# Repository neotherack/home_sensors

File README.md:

# Home Sensors

Monitorización ambiental de la casa con sensores ESP32, Prometheus y Grafana.

## Arquitectura

```
┌────────────────────────────────────────────────────────┐
│  ESP32 sensors (4)                                     │
│  ┌──────────┐ ┌──────────┐ ┌──────────┐ ┌──────────┐ │
│  │ Office   │ │ Master   │ │ Living   │ │ Kitchen  │ │
│  │ .178:8000│ │ .179:8000│ │ .180:8000│ │ .181:8000│ │
│  └────┬─────┘ └────┬─────┘ └────┬─────┘ └────┬─────┘ │
│       │            │            │            │        │
└───────┼────────────┼────────────┼────────────┼────────┘
        └──────┬─────┴─────┬─────┴─────┬──────┘
               │                         │
        ┌──────▼──────┐          ┌──────▼──────┐
        │  Prometheus  │          │   Grafana   │
        │  arrakis:9090│◄────────►│  (dashboard)│
        └─────────────┘          └─────────────┘
               │
        ┌──────▼──────┐
        │  Alertmanager│
        │  arrakis:9093│
        └─────────────┘
```

Todos los ESP32 exponen métricas Prometheus en `:8000/metrics`. Prometheus scrapea cada 5m.

## Sensores

| IP | Ubicación | Ambiente | Orientación | Sensores |
|---|---|---|---|---|
| `192.168.1.178:8000` | **Office** | indoor | west | BMP180 (temp, pres), DHT22 (temp, hum), MICS5524 (gas ppm) |
| `192.168.1.179:8000` | **Master bedroom** | indoor | east | DHT22 (temp, hum) |
| `192.168.1.180:8000` | **Living** | indoor | east | DHT22 (temp, hum) |
| `192.168.1.181:8000` | **Kitchen** | indoor | west | DHT22 (temp, hum) |

### Renombrado: backyard → master_bedroom

Al mudarse a Galapagar (dúplex, ático), el sensor que antes estaba en la terraza (`backyard`, outdoor) pasó al dormitorio principal (master bedroom, indoor). Como no se quería modificar el firmware del ESP32, se añadió un `relabel_config` en Prometheus que renombra la label `location="backyard"` a `location="master_bedroom"` para la IP `192.168.1.179`.

**Fichero:** `/etc/prometheus/prometheus.yml`:
```yaml
relabel_configs:
  - source_labels: [location, instance]
    target_label: location
    replacement: master_bedroom
    regex: backyard;.*179.*
    action: replace
```

Los datos históricos anteriores al cambio siguen con `location="backyard"` (se conserva el histórico real).

## Dashboard Grafana

**Weather Station** — exportado como `grafana-dashboard-weather-station.json`.

Paneles:
- **Active sensors** — cuenta de sensores activos (`sum(up{sensor!=""})`)
- **Estado Sensores** — `up` por ubicación
- **Indoor temperature** — temperatura media 5m por ubicación (con thresholds 15-30°C)
- **Indoor humidity** — humedad media 5m por ubicación
- **Air - Gases** — ppm del sensor MICS5524 (office), medias 5m y 6h
- **Pressure** — presión absoluta, medias 5m, 15d, 90d
- **Sea Level Pressure** — presión a nivel del mar (ver sección abajo)

### Sea Level Pressure

Dos queries:
- **`basic_raw`**: fórmula ISA estándar (asume 15°C exterior). Altitud 880m (Galapagar).
  ```
  avg_over_time(pressure[5m]) / (1 - (880 / 44330))^5.255
  ```
- **`complex_raw`** (actualmente sin datos): corrección con temperatura exterior real. Requiere un sensor outdoor que aún no se ha desplegado.
  ```
  P_abs * (T_real / (T_real - 0.0065 * 880))^5.255
  ```

### Recording rules (Prometheus)

Definidas en `/etc/prometheus/groups/weather.yml`:
- **`basic`** — presión relativa ISA (activa)
- **`advanced`** — comentada, pendiente de sensor outdoor

## Firmware ESP32

El código fuente está en este repo, ramas:

| Rama | Plataforma | Descripción |
|---|---|---|
| `main` | Raspberry Pi (Python) | Exporter original con BMP180 + DHT22. **Histórico/legacy**. |
| `sensors_trim` | Raspberry Pi (Python) | Mismo contenido que main. |
| `wemos_d1_mini` | ESP8266/ESP32 (Arduino) | Firmware completo con BMP180 + DHT22 + MICS5524. Incluye `config.h.TEMPLATE`. |

El firmware actualmente corriendo en los ESP32 usa un formato de métricas con labels (`temperature{sensor="DHT", location="..."}`) más moderno que el del repo. Está pendiente de sincronizar.

### Requisitos (RPi legacy)

```
adafruit-circuitpython-dht==4.0.6
smbus==1.1.post2
prometheus_client==0.21.1
```

## Infraestructura asociada

| Servicio | URL | Máquina |
|---|---|---|
| Prometheus | `https://prometheus.franvallejo.es` | arrakis |
| Prometheus (targets) | `https://prometheus.franvallejo.es/classic/targets` | arrakis |
| Grafana | Dashboard "Weather station" | arrakis |

Otros jobs en Prometheus: node_exporter, pgsql, pihole, unbound, fail2ban, jellyfin, twitter_metrics, jetson_gpu (down).

## Acceso API Grafana

Se ha creado un **Service Account** con rol **Viewer** para acceso programático:
- **Nombre:** `home_sensors_readonly`
- **Rol:** Viewer
- **Token:** generado en el momento de uso (no almacenado en el repo)

Para regenerar el token si expira, usar `create_grafana_token_simple.sh`.

## Pendientes

- [ ] Desplegar sensor outdoor (ESP32 solar + batería, ventana) para reactivar `complex_raw` en presión relativa
- [ ] Sincronizar el firmware actual de los ESP32 con este repo

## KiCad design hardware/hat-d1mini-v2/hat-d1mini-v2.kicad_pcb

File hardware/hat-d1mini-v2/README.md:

# HAT v2 universal para Wemos D1 mini (home_sensors)

**Estado: borrador v2.0.** Placa universal pensada para que cada nodo detecte sus
chips por I2C y reporte solo lo que tiene. Generada por script (`generate_hat.py`).

## Que es
- Placa con forma de shield que se encaja sobre el Wemos D1 mini (ESP8266).
- Conectores para llevar **cualquier combinacion** de sensores que manejamos:
  - I2C (dos conectores, para encadenar): AHT20+BMP280, ENS160+AHT21, SCD40, SGP40...
  - DHT22 (para reaprovechar los que ya hay).
  - Gas analogico (AOUT) con divisor y driver de heater.
- Pull-ups I2C y de DHT, proteccion ESD (TVS), divisor de medida de bateria,
  jumper de deep sleep (D0-RST) y conector de bateria + pads para modulo TP4056.

## Pinout del D1 mini usado
- `D1` (GPIO5) = **SCL**
- `D2` (GPIO4) = **SDA**
- `D5` (GPIO14) = **DHT (data)**
- `D6` (GPIO12) = **HEATER (gate Q1)** para sensor de gas analogico
- `A0` = **sense** (bateria o AOUT de gas, segun jumper)
- `D0` (GPIO16) = **jumper a RST** (deep sleep)
- `3V3`, `5V`, `G`

## Conectores
- `J1` / `J2`: JST-XH 4p I2C — `GND 3V3 SDA SCL` (dos, para encadenar el bus).
- `J3`: JST-XH 3p DHT22 — `3V3 DATA GND`.
- `J4`: JST-XH 4p gas — `5V GND AOUT HEAT`.
- `J5`: JST-XH 2p bateria — `B+ B-`.
- `J6`: tira 4p para modulo TP4056 — `IN+ IN- B+ B-`.

## Componentes
- `R1` `R2` 10k: pull-up I2C (a 3V3). `R3` 10k: pull-up DHT.
- `R4` 100k: serie para medir bateria en A0 (el A0 del D1 mini admite 0-3,2 V).
- `R5` 100k / `R6` 150k: divisor de la salida analogica de gas hacia A0.
- `R7` 1k: gate del MOSFET `Q1` (2N7000/AO3400) que apaga/enciende el heater.
- `D1..D4` TVS: proteccion ESD (SDA, SCL, DHT, A0).

## Ficheros
- `hat-d1mini-v2.kicad_pro/.kicad_sch/.kicad_pcb`: proyecto KiCad (importable en KiCad o EasyEDA).
- `gerbers/*.gbr` + `hat-d1mini-v2.drl`: para subir a PCBWay/JLCPCB.
- `gerbers/hat-d1mini-v2-gerbers.zip`: ZIP listo para el visor de gerbers de la fabrica.
- `images/hat-d1mini-v2_top.svg|.png`: previsualizacion de la placa y las pistas.
- `images/hat-d1mini-v2_schematic.svg|.png`: esquema de bloques (ilustrativo).

## AVISOS (leer antes de fabricar)
1. El **enrutado es orientativo** (ortogonal, sin DRC fina). Abrir en KiCad, lanzar el DRC
   y ajustar antes de fabricar.
2. **No he podido validar con `kicad-cli`** (no esta instalado en arrakis). Los `.kicad_*`
   son texto generado; revisar que abren bien en KiCad.
3. Los **gerbers** se han escrito a mano (RS-274X + Excellon). Conviene cargarlos en el
   visor online de PCBWay/JLCPCB (que valida el paquete) antes de pedir.
4. Falta decidir valores finales de algunos componentes (divisor de gas) en funcion del
   sensor que se monte.

## Regenerar
```
python3 generate_hat.py
```
(y, opcional, `magick -density 150 images/hat-d1mini-v2_top.svg -background white -flatten images/hat-d1mini-v2_top.png`)

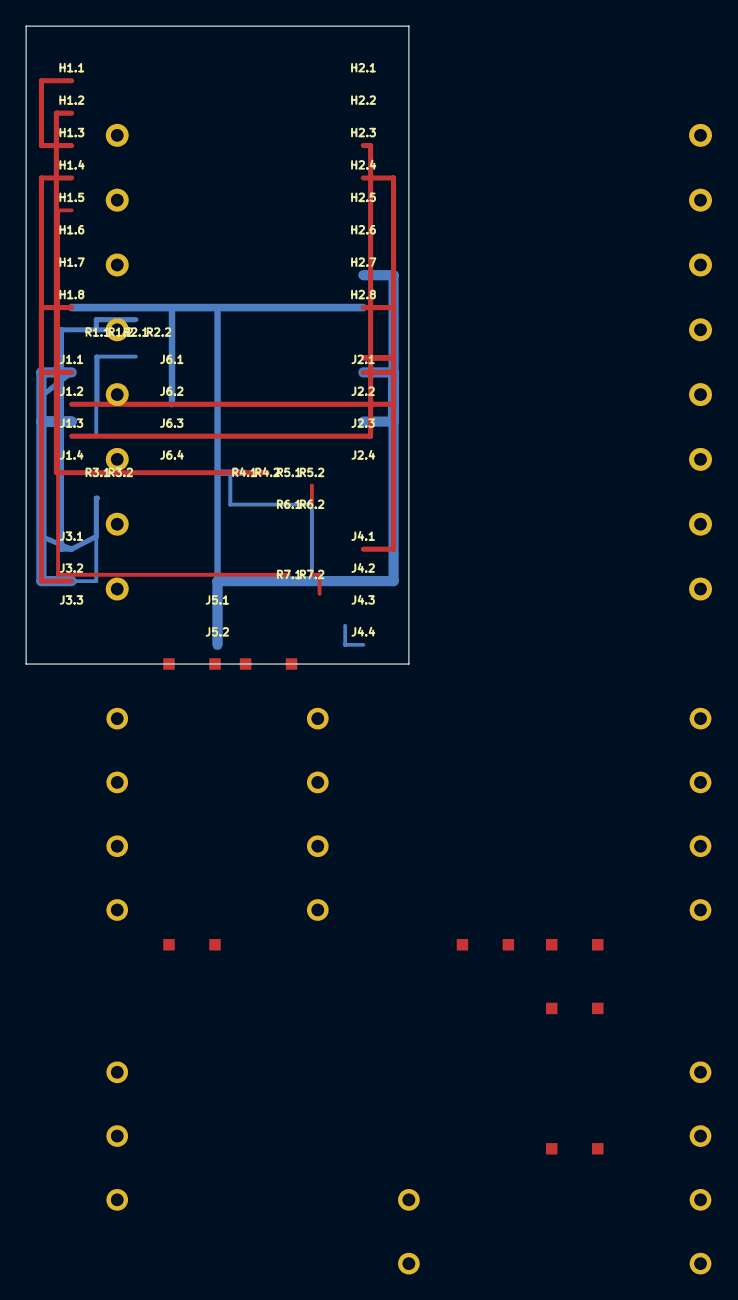
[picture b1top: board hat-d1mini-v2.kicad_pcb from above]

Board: 2 copper layers, 30.0 x 50.0 mm, 51 parts (0 on the bottom side), 10 nets.

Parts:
H1.1: PAD; H1.1
H1.2: PAD; H1.2
H1.3: PAD; H1.3
H1.4: PAD; H1.4
H1.5: PAD; H1.5
H1.6: PAD; H1.6
H1.7: PAD; H1.7
H1.8: PAD; H1.8
H2.1: PAD; H2.1
H2.2: PAD; H2.2
H2.3: PAD; H2.3
H2.4: PAD; H2.4
H2.5: PAD; H2.5
H2.6: PAD; H2.6
H2.7: PAD; H2.7
H2.8: PAD; H2.8
J1.1: PAD; J1.1
J1.2: PAD; J1.2
J1.3: PAD; J1.3
J1.4: PAD; J1.4
J2.1: PAD; J2.1
J2.2: PAD; J2.2
J2.3: PAD; J2.3
J2.4: PAD; J2.4
J3.1: PAD; J3.1
J3.2: PAD; J3.2
J3.3: PAD; J3.3
J4.1: PAD; J4.1
J4.2: PAD; J4.2
J4.3: PAD; J4.3
J4.4: PAD; J4.4
J5.1: PAD; J5.1
J5.2: PAD; J5.2
J6.1: PAD; J6.1
J6.2: PAD; J6.2
J6.3: PAD; J6.3
J6.4: PAD; J6.4
R1.1: PAD; R1.1
R1.2: PAD; R1.2
R2.1: PAD; R2.1
R2.2: PAD; R2.2
R3.1: PAD; R3.1
R3.2: PAD; R3.2
R4.1: PAD; R4.1
R4.2: PAD; R4.2
R5.1: PAD; R5.1
R5.2: PAD; R5.2
R6.1: PAD; R6.1
R6.2: PAD; R6.2
R7.1: PAD; R7.1
R7.2: PAD; R7.2

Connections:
3V3: H1.8.1, J1.2.1, J2.2.1, J3.1.1, R1.1.1, R2.1.1, R3.1.1
5V: H2.8.1, J4.1.1, J6.1.1
A0: H1.2.1, J4.3.1, R4.2.1, R5.1.1
AOU_T: R5.2.1, R6.1.1
DHT: H1.4.1, J3.2.1, R3.2.1
GND: H2.7.1, J1.1.1, J2.1.1, J3.3.1, J4.2.1, J5.2.1, J6.2.1, J6.4.1, R6.2.1
HEAT: H1.5.1, J4.4.1, R7.1.1
SCL: H2.3.1, J1.4.1, J2.4.1, R2.2.1
SDA: H2.4.1, J1.3.1, J2.3.1, R1.2.1
VBAT: J5.1.1, J6.3.1, R4.1.1

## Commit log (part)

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2024-12-29 added readme
2024-12-29 fix name on photo
2025-01-07 post-christmas update, added prometheus exporter
2025-01-07 chart screenshot
2025-01-07 wiring pics
2025-01-07 manual adjust on values for sensors at the python prometheus exporter
2025-01-07 minor adjust
2026-06-17 feat: documentacion inicial, dashboard Grafana y config Prometheus
2026-06-17 update: dashboard JSON desde live Grafana (version 95)
2026-06-17 fix: air panel - 1h avg instead of 6h, added stddev
2026-06-17 fix: dual axis for air-stddev on right Y
2026-06-17 fix: split air panel - stddev to separate chart
2026-06-17 feat: shield v1 design files (schematic, BOM, EasyEDA, layout)
2026-06-17 feat: shield v1 KiCad project + ZIP (EasyEDA importable)
